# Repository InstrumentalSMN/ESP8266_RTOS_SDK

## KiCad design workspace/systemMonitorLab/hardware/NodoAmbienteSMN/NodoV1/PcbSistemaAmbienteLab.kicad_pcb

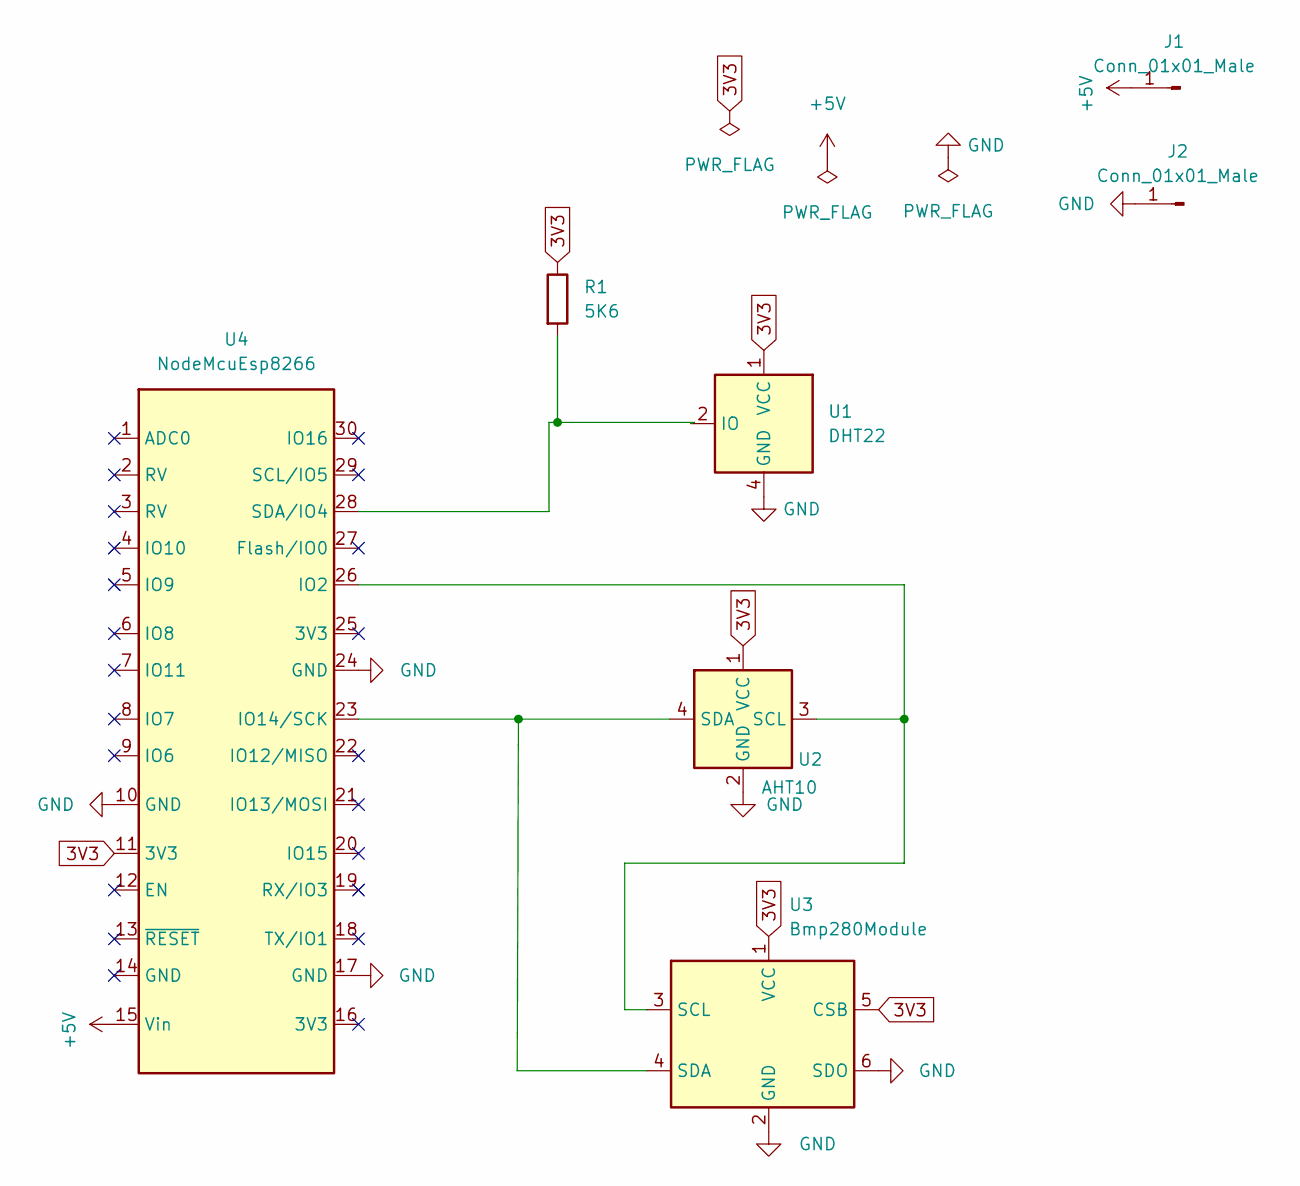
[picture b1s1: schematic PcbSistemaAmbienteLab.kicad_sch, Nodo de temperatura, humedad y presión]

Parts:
J1, J2: Conn_01x01_Male; Pin_D1.0mm_L10.0mm
R1: 5K6; R_Axial_DIN0207_L6.3mm_D2.5mm_P15.24mm_Horizontal
U1: DHT22; Aosong_DHT11_5.5x12.0_P2.54mm
U2: AHT10; PinHeader_1x04_P2.54mm_Vertical
U3: Bmp280Module; PinHeader_1x06_P2.54mm_Vertical
U4: NodeMcuEsp8266; ESP8266

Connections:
3V3: R1.1, U1.1 (VCC), U2.1 (VCC), U3.1 (VCC), U3.5 (CSB), U4.11 (3V3)
+5V: J1.1, U4.15 (Vin)
GND: J2.1, U1.4 (GND), U2.2 (GND), U3.2 (GND), U3.6 (SDO), U4.10 (GND), U4.17 (GND), U4.24 (GND)
unnamed: R1.2, U1.2 (IO), U4.28 (SDA/IO4)
unnamed: U2.3 (SCL), U3.3 (SCL), U4.26 (IO2)
unnamed: U2.4 (SDA), U3.4 (SDA), U4.23 (IO14/SCK)

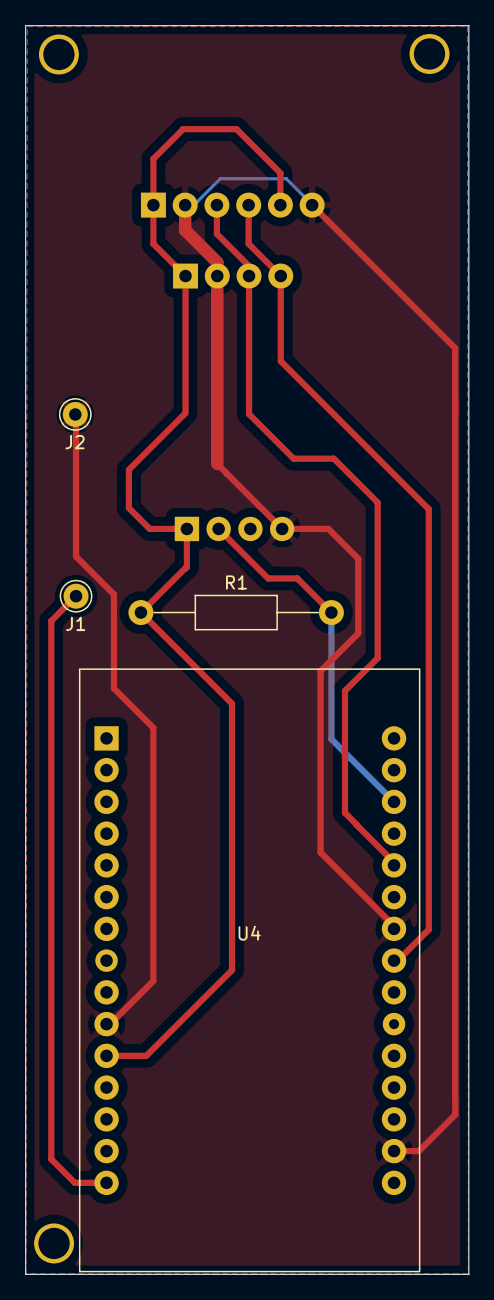
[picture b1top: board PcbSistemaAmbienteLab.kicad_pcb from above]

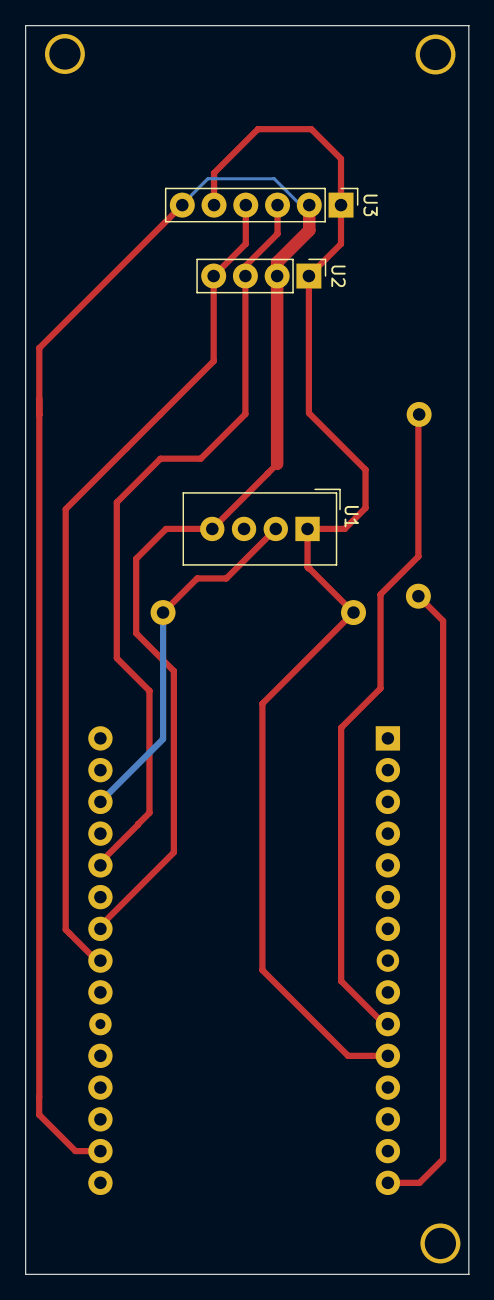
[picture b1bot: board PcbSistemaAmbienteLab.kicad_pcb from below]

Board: 2 copper layers, 35.5 x 99.9 mm, 7 parts (3 on the bottom side), 6 nets.

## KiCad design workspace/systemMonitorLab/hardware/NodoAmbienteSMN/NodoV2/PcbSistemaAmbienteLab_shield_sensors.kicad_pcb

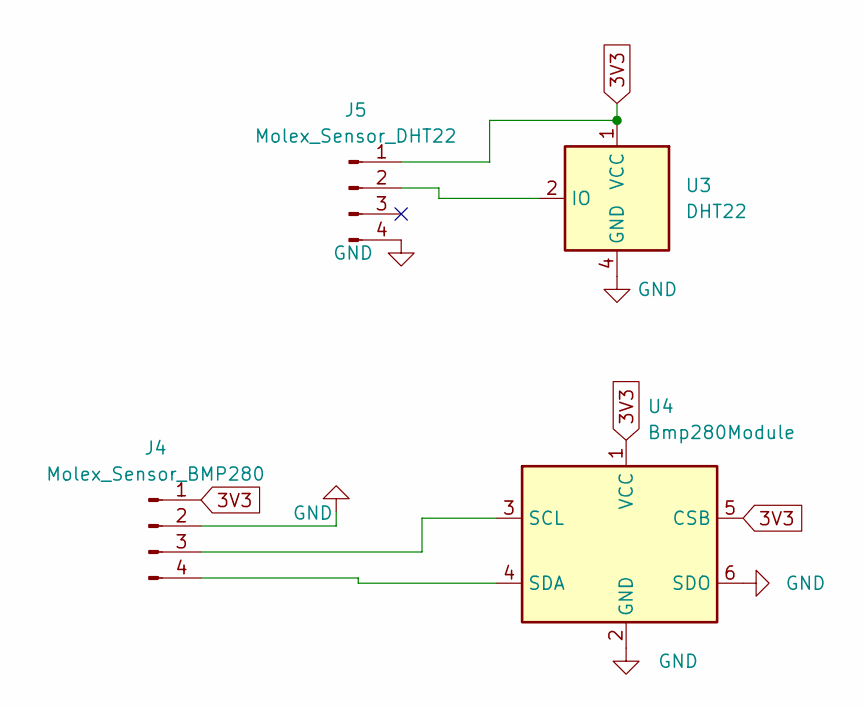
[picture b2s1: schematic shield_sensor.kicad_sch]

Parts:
J4: Molex_Sensor_BMP280; PinHeader_1x04_P2.54mm_Horizontal
J5: Molex_Sensor_DHT22; PinHeader_1x04_P2.54mm_Horizontal
U3: DHT22; Aosong_DHT11_5.5x12.0_P2.54mm
U4: Bmp280Module; BMP280_Module

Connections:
3V3: J4.1, J5.1, U3.1 (VCC), U4.1 (VCC), U4.5 (CSB)
GND: J4.2, J5.4, U3.4 (GND), U4.2 (GND), U4.6 (SDO)
unnamed: J4.3, U4.3 (SCL)
unnamed: J4.4, U4.4 (SDA)
unnamed: J5.2, U3.2 (IO)

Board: 2 copper layers, 4 parts (0 on the bottom side), 5 nets, no tracks yet.

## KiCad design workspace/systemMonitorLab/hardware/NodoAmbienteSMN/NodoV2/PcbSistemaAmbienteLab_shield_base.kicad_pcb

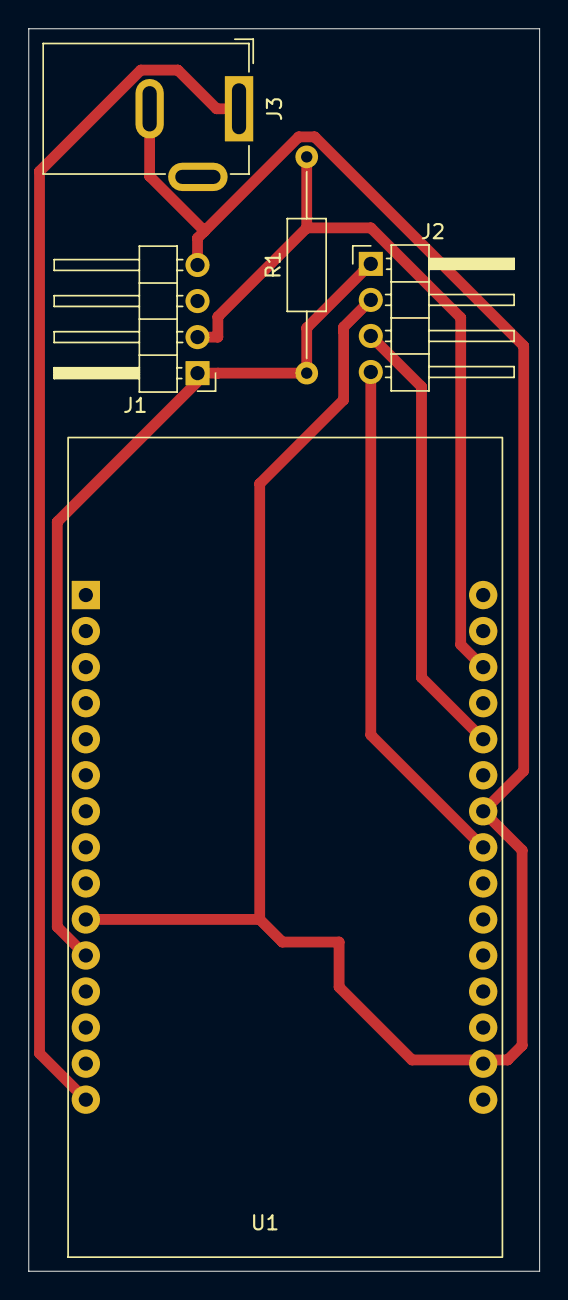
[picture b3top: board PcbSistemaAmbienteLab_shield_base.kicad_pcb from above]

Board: 2 copper layers, 36.0 x 87.6 mm, 5 parts (0 on the bottom side), 6 nets.

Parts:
J1: Molex_MainBoard_DHT22; PinHeader_1x04_P2.54mm_Horizontal
J2: Molex_MainBoard_BMP280; PinHeader_1x04_P2.54mm_Horizontal
J3: Jack-DC; BarrelJack_GCT_DCJ200-10-A_Horizontal
R1: 5K6; R_Axial_DIN0207_L6.3mm_D2.5mm_P15.24mm_Horizontal
U1: NodeMcuEsp8266; ESP8266_v3

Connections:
3V3: J1.1, J2.1, R1.1, U1.11 (3V3)
+5V: J3.1, U1.15 (Vin)
/shield_base/SCL: J2.3, U1.26 (IO2)
/shield_base/SDA: J2.4, U1.23 (IO14/SCK)
GND: J1.4, J2.2, J3.2, U1.10 (GND), U1.17 (GND), U1.24 (GND)
unnamed: J1.2, R1.2, U1.28 (SDA/IO4)

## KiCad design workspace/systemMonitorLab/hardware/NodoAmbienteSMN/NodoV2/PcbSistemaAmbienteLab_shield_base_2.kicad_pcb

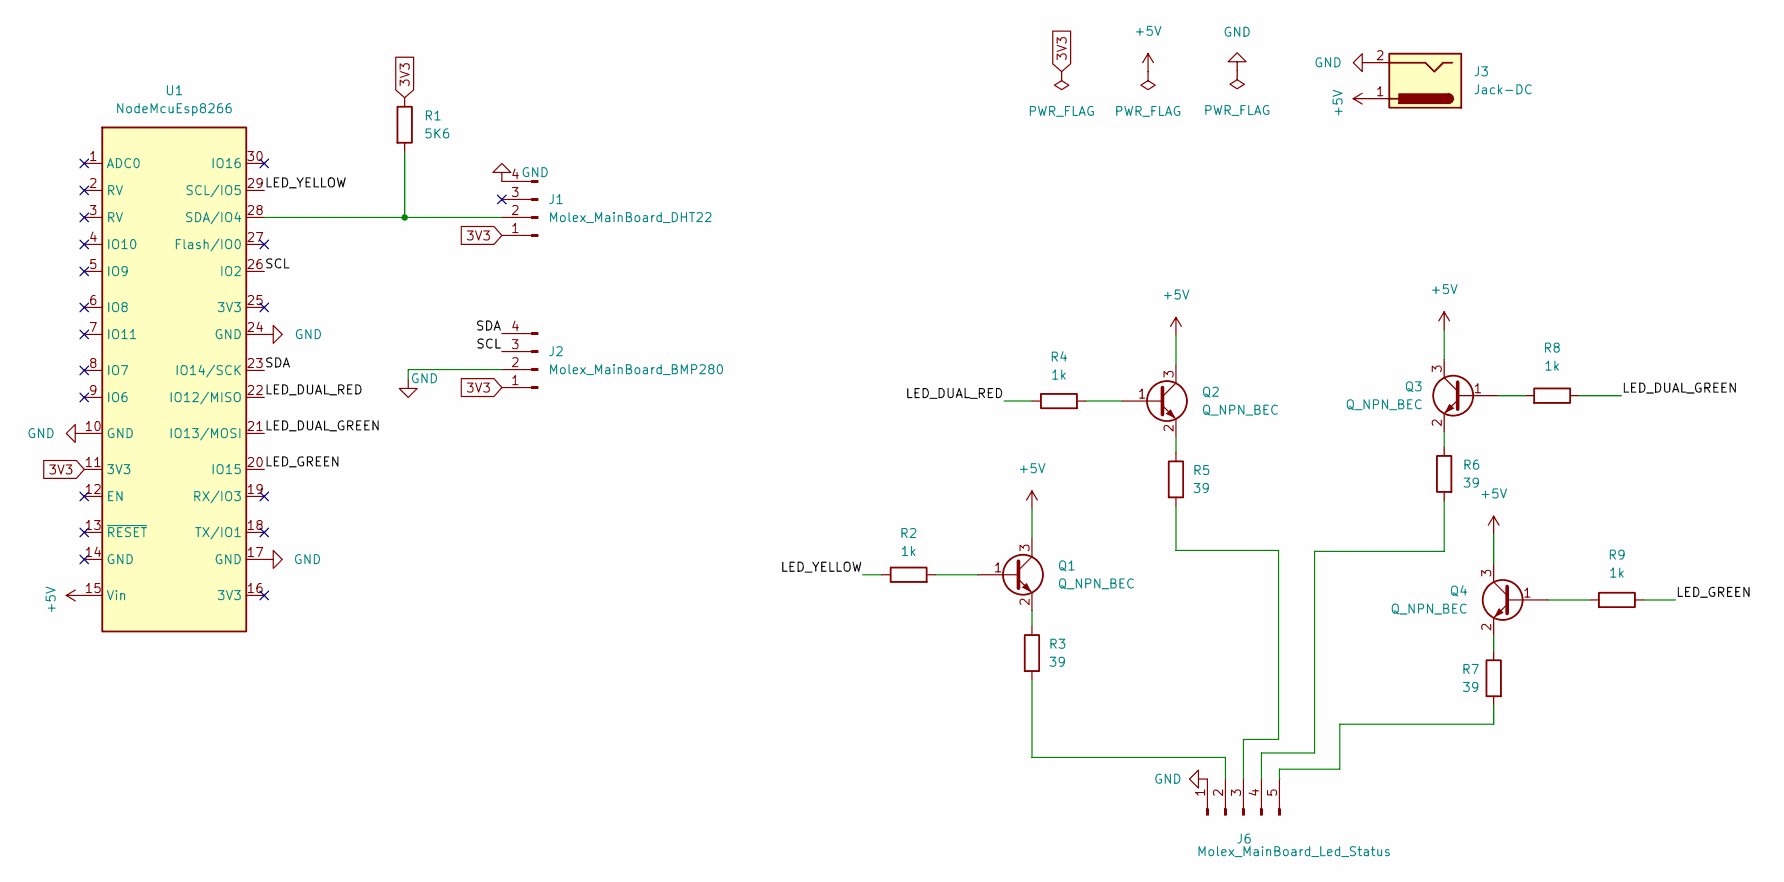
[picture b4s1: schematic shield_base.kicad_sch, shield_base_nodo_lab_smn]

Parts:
J1: Molex_MainBoard_DHT22; PinHeader_1x04_P2.54mm_Horizontal
J2: Molex_MainBoard_BMP280; PinHeader_1x04_P2.54mm_Horizontal
J3: Jack-DC; BarrelJack_GCT_DCJ200-10-A_Horizontal
J6: Molex_MainBoard_Led_Status; PinHeader_1x05_P2.54mm_Horizontal
Q1, Q2, Q3, Q4: Q_NPN_BEC; SOT-23
R1: 5K6; R_1206_3216Metric
R2, R4, R8, R9: 1k; R_1206_3216Metric
R3, R5, R6, R7: 39; R_1206_3216Metric
U1: NodeMcuEsp8266; ESP8266_v3

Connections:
3V3: J1.1, J2.1, R1.1, U1.11 (3V3)
+5V: J3.1, Q1.3 (C), Q2.3 (C), Q3.3 (C), Q4.3 (C), U1.15 (Vin)
/shield_base/LED_DUAL_GREEN: R8.1, U1.21 (IO13/MOSI)
/shield_base/LED_DUAL_RED: R4.1, U1.22 (IO12/MISO)
/shield_base/LED_GREEN: R9.1, U1.20 (IO15)
/shield_base/LED_YELLOW: R2.1, U1.29 (SCL/IO5)
/shield_base/SCL: J2.3, U1.26 (IO2)
/shield_base/SDA: J2.4, U1.23 (IO14/SCK)
GND: J1.4, J2.2, J3.2, J6.1, U1.10 (GND), U1.17 (GND), U1.24 (GND)
unnamed: J1.2, R1.2, U1.28 (SDA/IO4)
unnamed: J6.2, R3.2
unnamed: J6.3, R5.2
unnamed: J6.4, R6.2
unnamed: J6.5, R7.2
unnamed: Q1.1 (B), R2.2
unnamed: Q1.2 (E), R3.1
unnamed: Q2.1 (B), R4.2
unnamed: Q2.2 (E), R5.1
unnamed: Q3.1 (B), R8.2
unnamed: Q3.2 (E), R6.1
unnamed: Q4.1 (B), R9.2
unnamed: Q4.2 (E), R7.1

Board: 2 copper layers, 18 parts (13 on the bottom side), 22 nets, no tracks yet.

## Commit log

2023-06-12 Inicio de proyecto en workspace
2023-07-05 Se sube los archvios .c y .h para leer y mostrar los datos del sensor AHT10
2023-07-07 Version 1.0 de firmware para enviar datos de los termohigrometros a un servidor crudo TCP/IP local cada 10 segundos
2023-07-21 Se agrego los sensores AHT10 y BMP280 por i2c y DHT22 por protocolo propio, trasminte a un sever local
2023-07-31 Subo el desarrollo de PCB para el ESP8266 con los sensores y perifericos necesarios
2023-08-02 Esquemativo v1.0 y PCB v1.0
2023-08-03 Esquematico y PCB para sistema de monitoreo v1.1
2023-08-14 subo v1.2 del PCB del sistema de monitoreo ambiente, esta versión se utilizara para calibrar el sensor AHT10 vs DHT22
2023-09-05 Dejo transmitiendo cada 1 minuto
2023-10-03 Se agregar las correcciones para cada sensor a partir de la calibración de temperatura y humedad y para presino se agrega 1 hPa dando buenos resultados de comparación frente a un patrón
2025-01-15 Se agrega la conexion con un servidor WebSocket y sus correspondientes codificadores de mensajes de 125 y 126
2025-02-10 Se agrego la primer version del firmware v1.0, que envia las mediciones de temp, rh y presión con un intervalo de tiempo configurable
2025-02-17 Subimo la version 2 de la PCB de nodo ambiente.
2025-02-21 Se agregan leds de estado con sus respectivos conectores y se agrega en el codigo la configuracion de los GPIO para usar estos leds como indicadores de envio de datos, conexion con el servidor Web So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
2025-02-24 Se agrego una simulacion para manejar un pwm
